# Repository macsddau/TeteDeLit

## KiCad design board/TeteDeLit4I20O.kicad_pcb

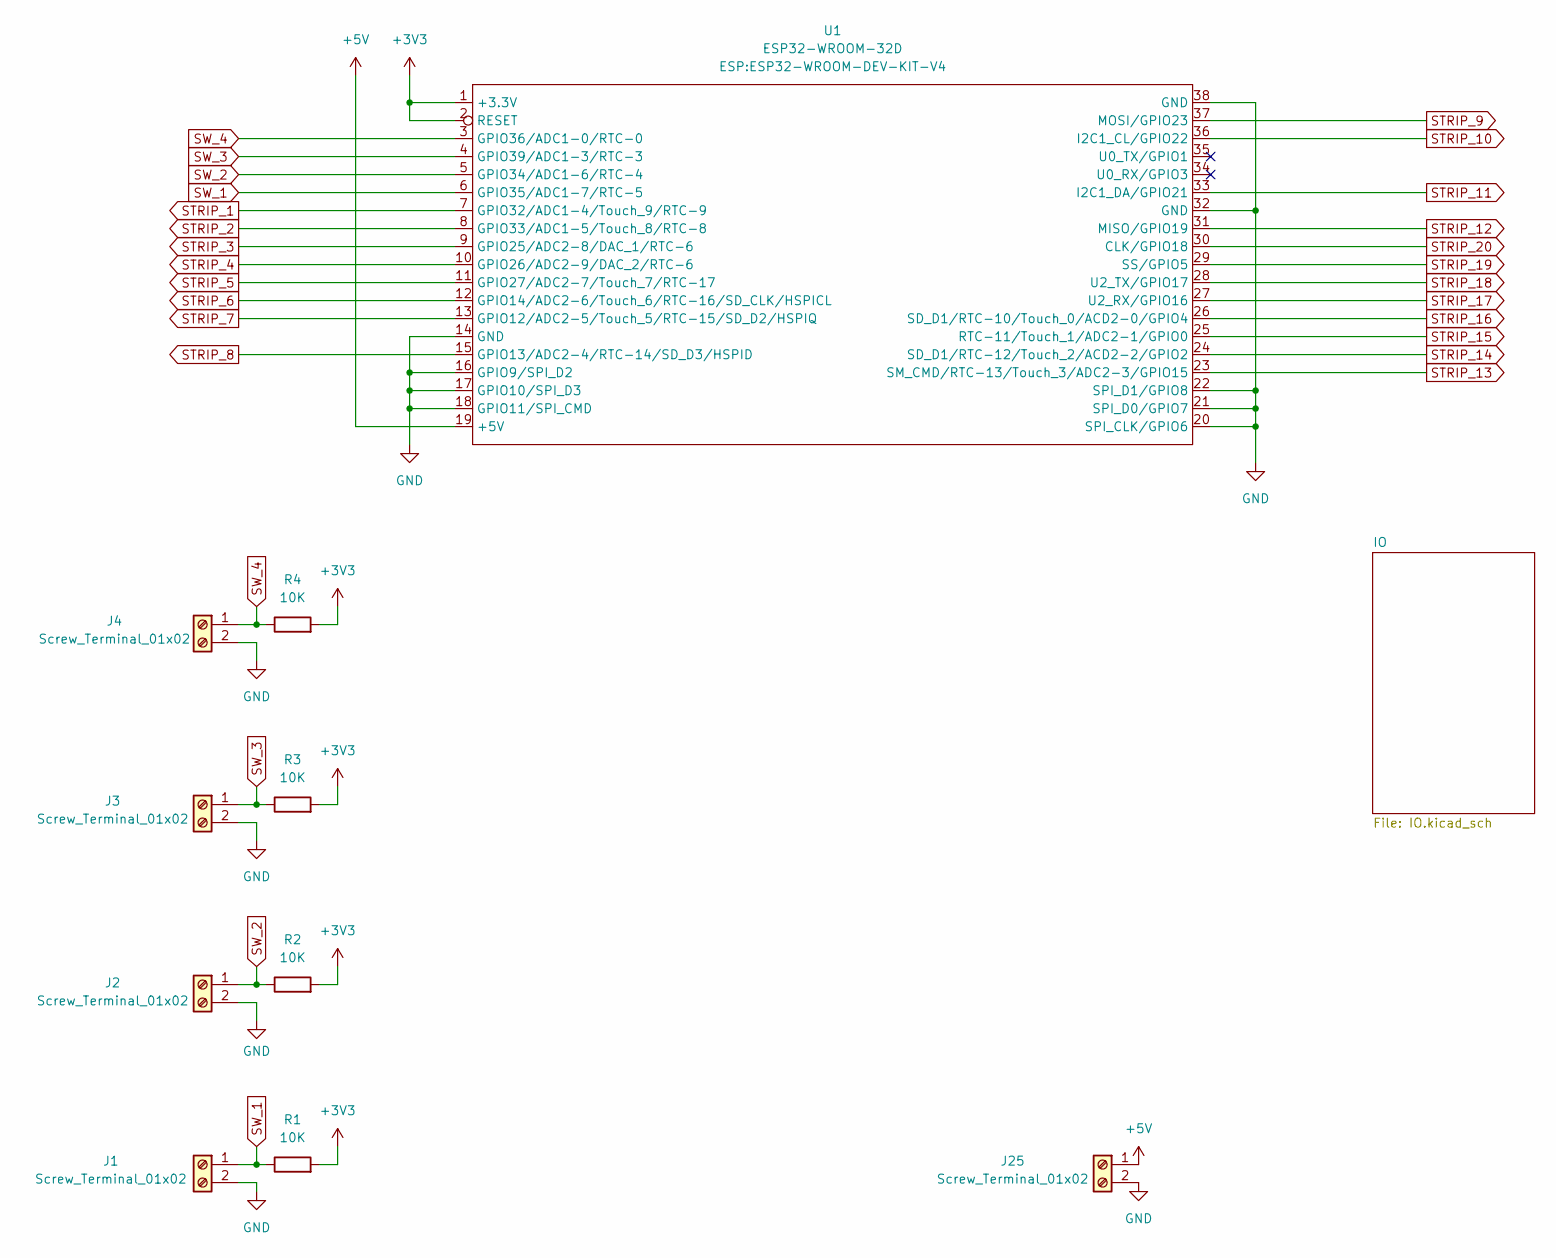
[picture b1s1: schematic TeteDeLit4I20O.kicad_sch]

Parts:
J1, J2, J3, J4, J25: Screw_Terminal_01x02; TerminalBlock_Phoenix_MPT-0,5-2-2.54_1x02_P2.54mm_Horizontal
R1, R2, R3, R4: 10K; R_Axial_DIN0204_L3.6mm_D1.6mm_P5.08mm_Horizontal
U1: ESP32-WROOM-32D; ESP32-WROOM-DEV-KIT-V4

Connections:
+3V3: R1.2, R2.2, R3.2, R4.2, U1.1 (+3.3V), U1.2 (RESET)
+5V: J25.1, U1.19 (+5V); also elsewhere on the board
GND: J1.2, J2.2, J3.2, J4.2, J25.2, U1.14 (GND), U1.16 (GPIO9/SPI_D2), U1.17 (GPIO10/SPI_D3), U1.18 (GPIO11/SPI_CMD), U1.20 (SPI_CLK/GPIO6), U1.21 (SPI_D0/GPIO7), U1.22 (SPI_D1/GPIO8), U1.32 (GND), U1.38 (GND); also elsewhere on the board
STRIP_1: U1.7 (GPIO32/ADC1-4/Touch_9/RTC-9); also elsewhere on the board
STRIP_2: U1.8 (GPIO33/ADC1-5/Touch_8/RTC-8); also elsewhere on the board
STRIP_3: U1.9 (GPIO25/ADC2-8/DAC_1/RTC-6); also elsewhere on the board
STRIP_4: U1.10 (GPIO26/ADC2-9/DAC_2/RTC-6); also elsewhere on the board
STRIP_5: U1.11 (GPIO27/ADC2-7/Touch_7/RTC-17); also elsewhere on the board
STRIP_6: U1.12 (GPIO14/ADC2-6/Touch_6/RTC-16/SD_CLK/HSP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); also elsewhere on the board
STRIP_7: U1.13 (GPIO12/ADC2-5/Touch_5/RTC-15/SD_D2/HSPIQ); also elsewhere on the board
STRIP_8: U1.15 (GPIO13/ADC2-4/RTC-14/SD_D3/HSPID); also elsewhere on the board
STRIP_9: U1.37 (MOSI/GPIO23); also elsewhere on the board
STRIP_10: U1.36 (I2C1_CL/GPIO22); also elsewhere on the board
STRIP_11: U1.33 (I2C1_DA/GPIO21); also elsewhere on the board
STRIP_12: U1.31 (MISO/GPIO19); also elsewhere on the board
STRIP_13: U1.23 (SM_CMD/RTC-13/Touch_3/ADC2-3/GPIO15); also elsewhere on the board
STRIP_14: U1.24 (SD_D1/RTC-12/Touch_2/ACD2-2/GPIO2); also elsewhere on the board
STRIP_15: U1.25 (RTC-11/Touch_1/ADC2-1/GPIO0); also elsewhere on the board
STRIP_16: U1.26 (SD_D1/RTC-10/Touch_0/ACD2-0/GPIO4); also elsewhere on the board
STRIP_17: U1.27 (U2_RX/GPIO16); also elsewhere on the board
STRIP_18: U1.28 (U2_TX/GPIO17); also elsewhere on the board
STRIP_19: U1.29 (SS/GPIO5); also elsewhere on the board
STRIP_20: U1.30 (CLK/GPIO18); also elsewhere on the board
SW_1: J1.1, R1.1, U1.6 (GPIO35/ADC1-7/RTC-5)
SW_2: J2.1, R2.1, U1.5 (GPIO34/ADC1-6/RTC-4)
SW_3: J3.1, R3.1, U1.4 (GPIO39/ADC1-3/RTC-3)
SW_4: J4.1, R4.1, U1.3 (GPIO36/ADC1-0/RTC-0)

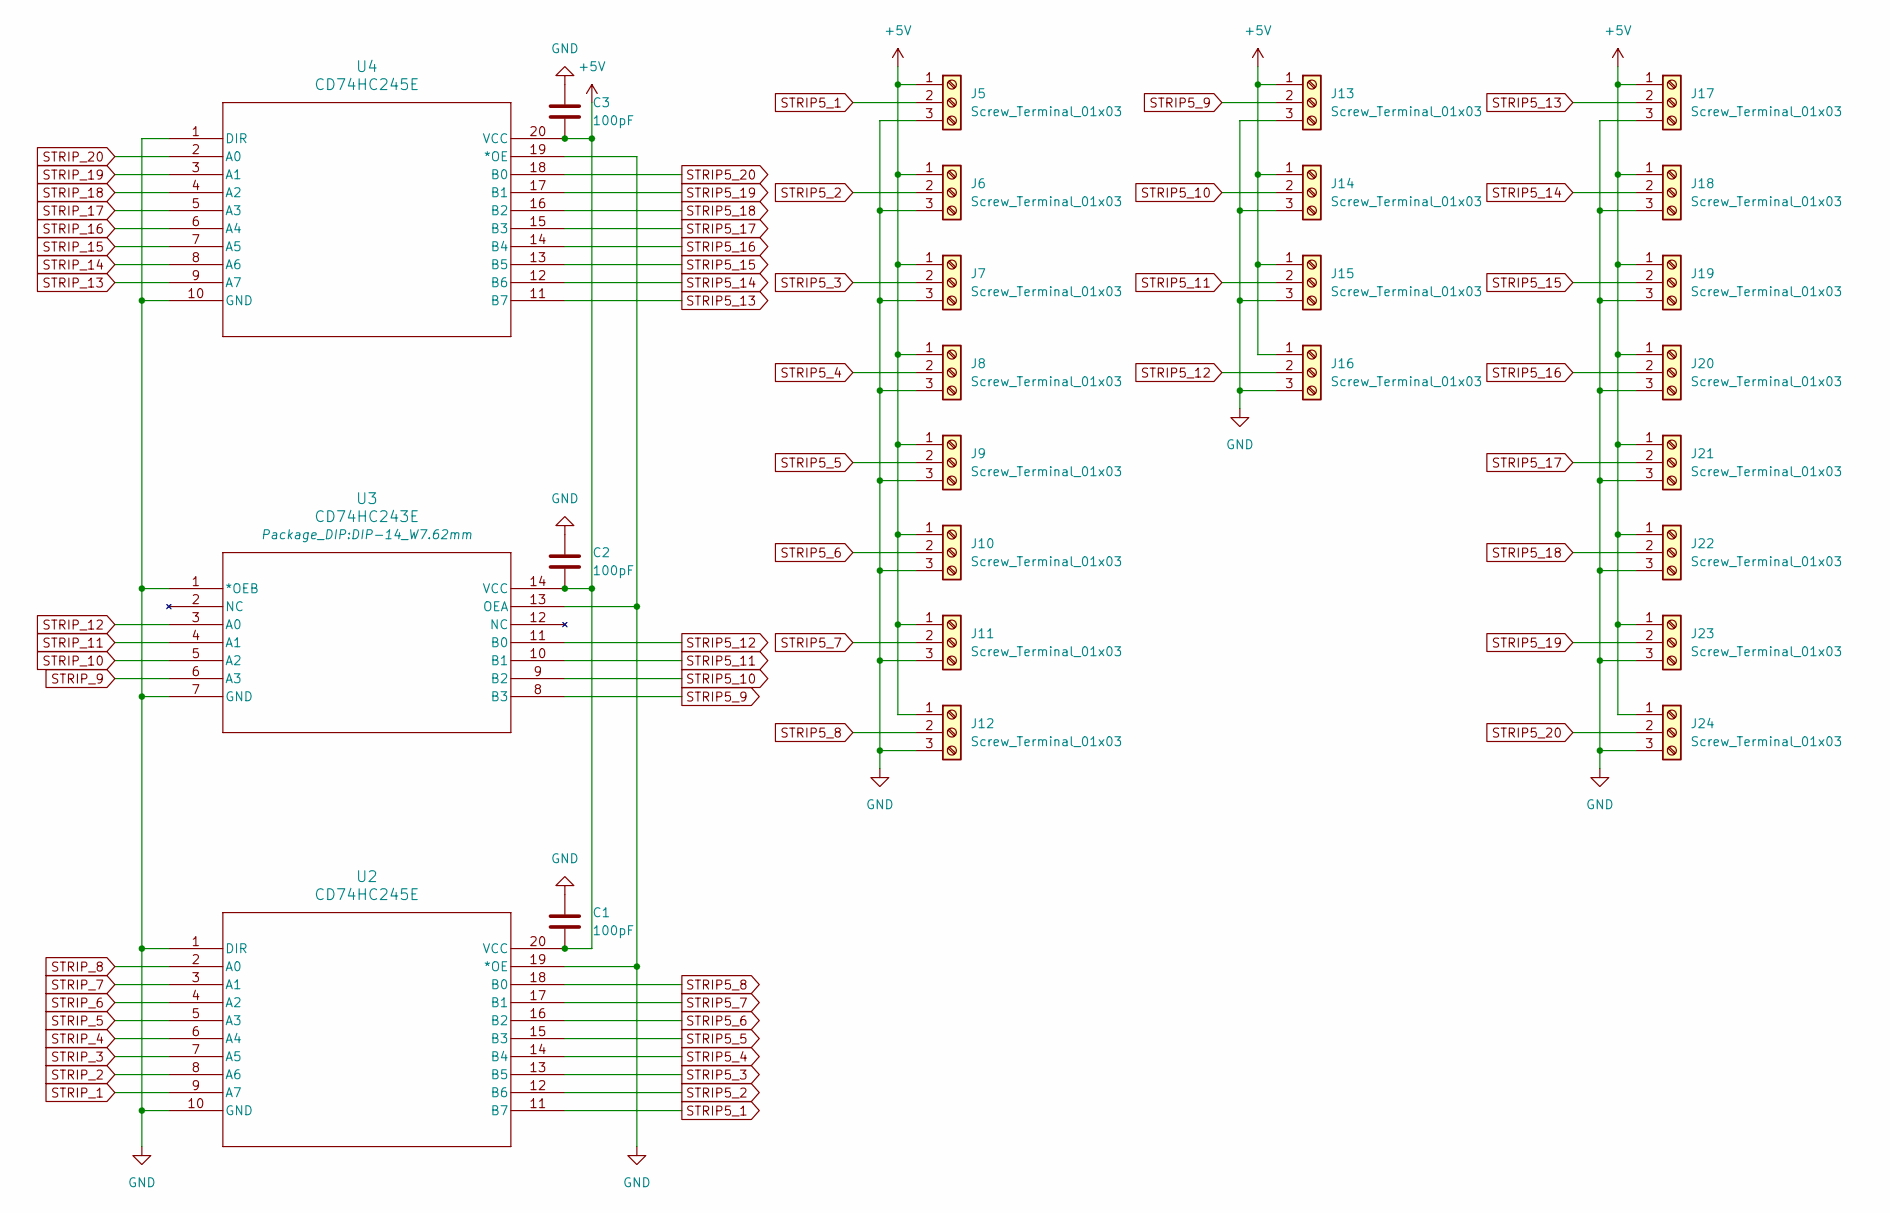
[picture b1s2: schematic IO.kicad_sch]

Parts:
C1, C2, C3: 100pF; C_Disc_D5.0mm_W2.5mm_P2.50mm
J5, J6, J7, J8, J9, J10, J11, J12, J13, J14, J15, J16, J17, J18, J19, J20, J21, J22, J23, J24: Screw_Terminal_01x03; TerminalBlock_Phoenix_MPT-0,5-3-2.54_1x03_P2.54mm_Horizontal
U2, U4: CD74HC245E; DIP-20_W7.62mm
U3: CD74HC243E; DIP-14_W7.62mm

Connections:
+5V: C1.2, C2.2, C3.2, J5.1, J6.1, J7.1, J8.1, J9.1, J10.1, J11.1, J12.1, J13.1, J14.1, J15.1, J16.1, J17.1, J18.1, J19.1, J20.1, J21.1, J22.1, J23.1, J24.1, U2.20 (VCC), U3.14 (VCC), U4.20 (VCC); also elsewhere on the board
GND: C1.1, C2.1, C3.1, J5.3, J6.3, J7.3, J8.3, J9.3, J10.3, J11.3, J12.3, J13.3, J14.3, J15.3, J16.3, J17.3, J18.3, J19.3, J20.3, J21.3, J22.3, J23.3, J24.3, U2.1 (DIR), U2.10 (GND), U2.19 (*OE), U3.1 (*OEB), U3.7 (GND), U3.13 (OEA), U4.1 (DIR), U4.10 (GND), U4.19 (*OE); also elsewhere on the board
STRIP5_1: J5.2, U2.11 (B7)
STRIP5_2: J6.2, U2.12 (B6)
STRIP5_3: J7.2, U2.13 (B5)
STRIP5_4: J8.2, U2.14 (B4)
STRIP5_5: J9.2, U2.15 (B3)
STRIP5_6: J10.2, U2.16 (B2)
STRIP5_7: J11.2, U2.17 (B1)
STRIP5_8: J12.2, U2.18 (B0)
STRIP5_9: J13.2, U3.8 (B3)
STRIP5_10: J14.2, U3.9 (B2)
STRIP5_11: J15.2, U3.10 (B1)
STRIP5_12: J16.2, U3.11 (B0)
STRIP5_13: J17.2, U4.11 (B7)
STRIP5_14: J18.2, U4.12 (B6)
STRIP5_15: J19.2, U4.13 (B5)
STRIP5_16: J20.2, U4.14 (B4)
STRIP5_17: J21.2, U4.15 (B3)
STRIP5_18: J22.2, U4.16 (B2)
STRIP5_19: J23.2, U4.17 (B1)
STRIP5_20: J24.2, U4.18 (B0)
STRIP_1: U2.9 (A7); also elsewhere on the board
STRIP_2: U2.8 (A6); also elsewhere on the board
STRIP_3: U2.7 (A5); also elsewhere on the board
STRIP_4: U2.6 (A4); also elsewhere on the board
STRIP_5: U2.5 (A3); also elsewhere on the board
STRIP_6: U2.4 (A2); also elsewhere on the board
STRIP_7: U2.3 (A1); also elsewhere on the board
STRIP_8: U2.2 (A0); also elsewhere on the board
STRIP_9: U3.6 (A3); also elsewhere on the board
STRIP_10: U3.5 (A2); also elsewhere on the board
STRIP_11: U3.4 (A1); also elsewhere on the board
STRIP_12: U3.3 (A0); also elsewhere on the board
STRIP_13: U4.9 (A7); also elsewhere on the board
STRIP_14: U4.8 (A6); also elsewhere on the board
STRIP_15: U4.7 (A5); also elsewhere on the board
STRIP_16: U4.6 (A4); also elsewhere on the board
STRIP_17: U4.5 (A3); also elsewhere on the board
STRIP_18: U4.4 (A2); also elsewhere on the board
STRIP_19: U4.3 (A1); also elsewhere on the board
STRIP_20: U4.2 (A0); also elsewhere on the board

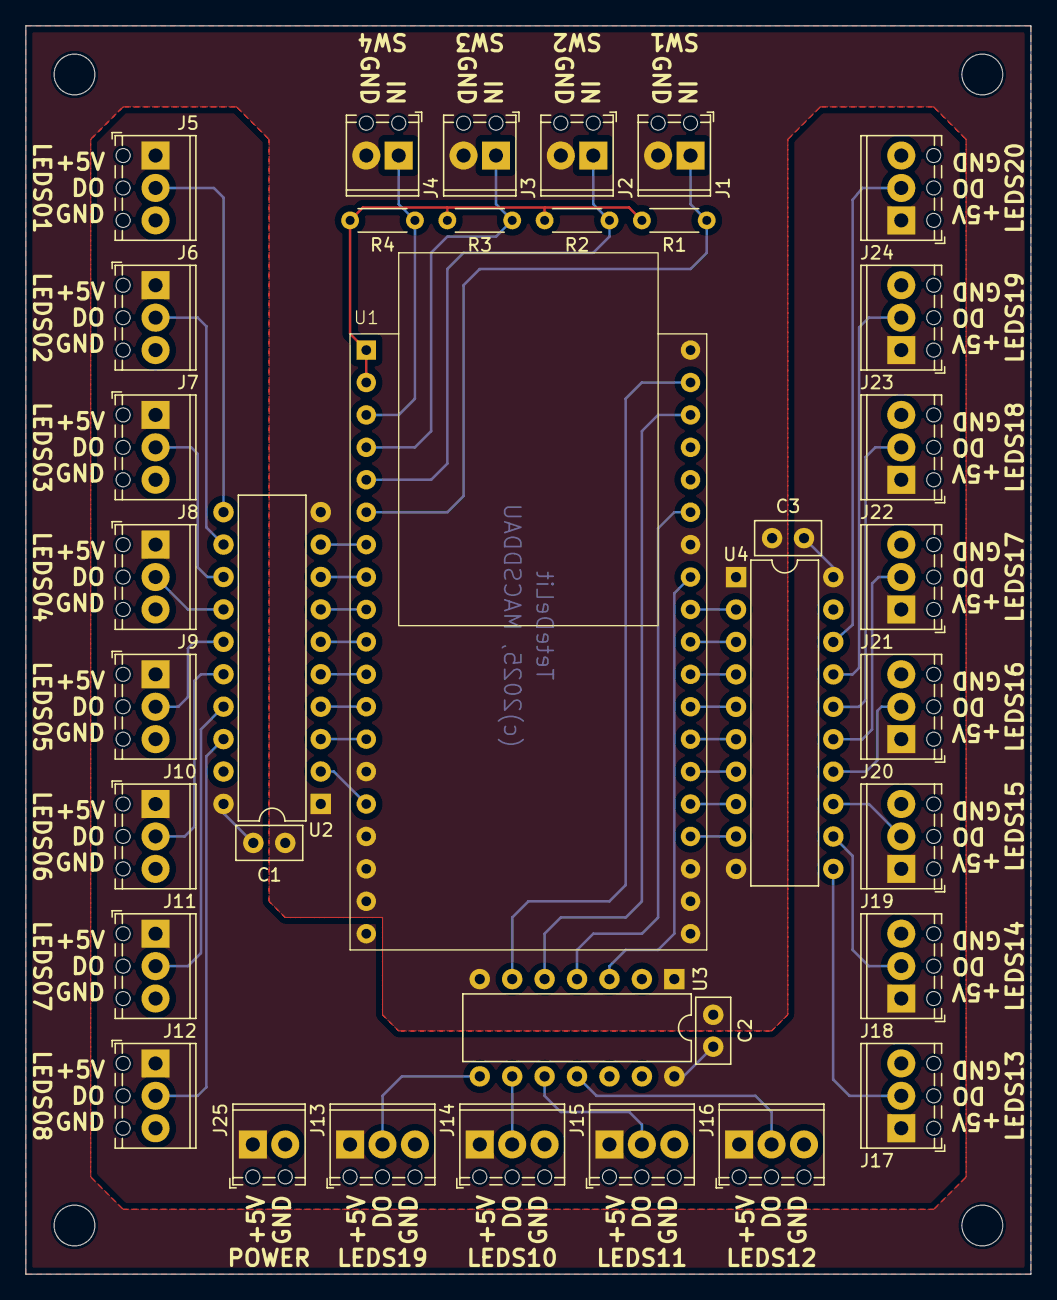
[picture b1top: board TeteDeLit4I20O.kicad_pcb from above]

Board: 2 copper layers, 78.7 x 97.8 mm, 40 parts (0 on the bottom side), 47 nets.

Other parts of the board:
VIS1, VIS2, VIS3, VIS4: MountingHole_3.2mm_M3_DIN965

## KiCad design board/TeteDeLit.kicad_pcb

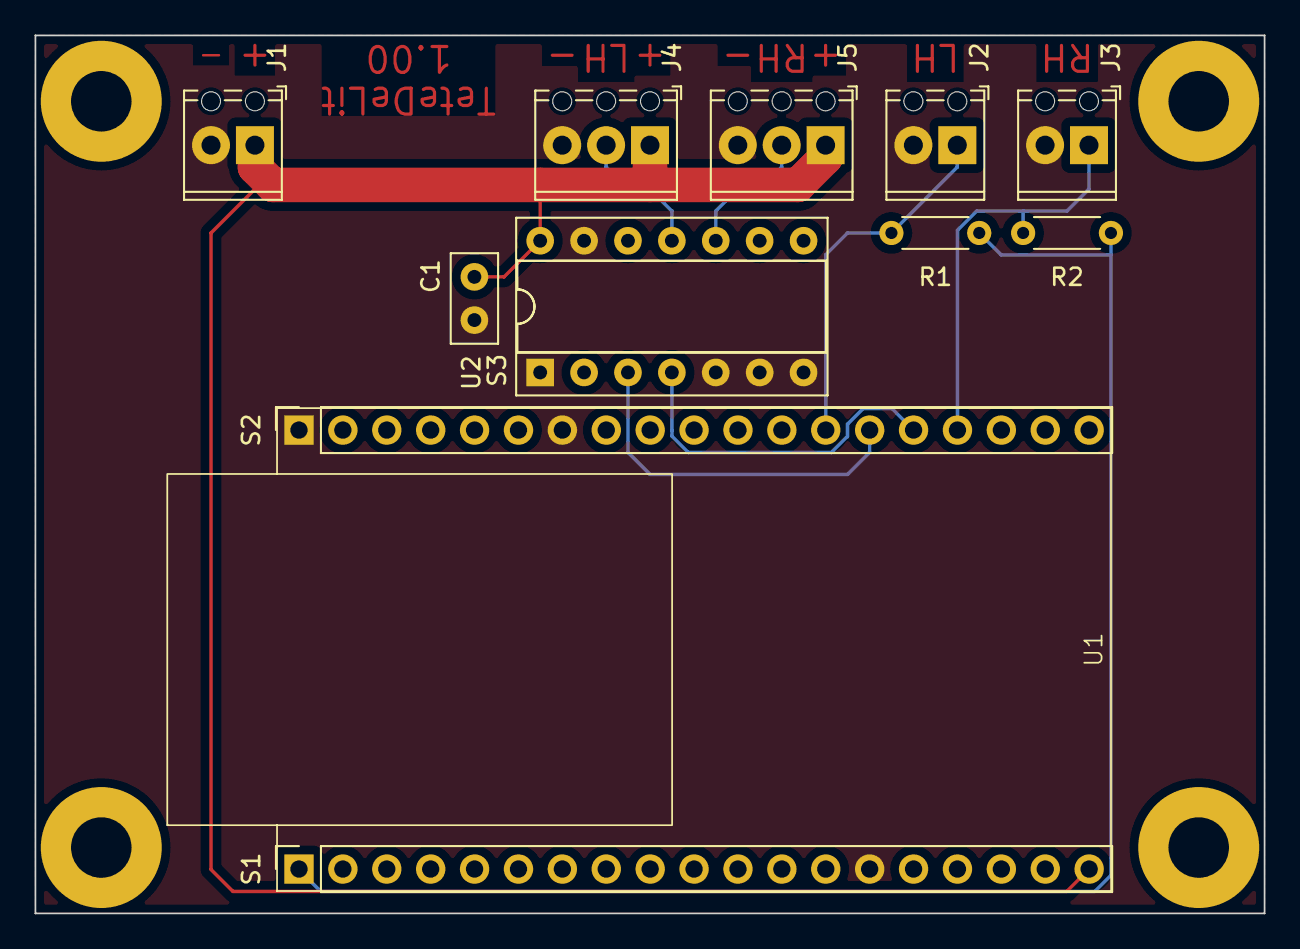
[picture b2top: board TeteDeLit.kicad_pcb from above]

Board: 2 copper layers, 71.1 x 50.8 mm, 17 parts (0 on the bottom side), 9 nets.

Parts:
C1: C; C_Disc_D5.0mm_W2.5mm_P2.50mm
J1, J2, J3: Screw_Terminal_01x02; TerminalBlock_Phoenix_MPT-0,5-2-2.54_1x02_P2.54mm_Horizontal
J4, J5: Screw_Terminal_01x03; TerminalBlock_Phoenix_MPT-0,5-3-2.54_1x03_P2.54mm_Horizontal
R1, R2: R10K; R_Axial_DIN0204_L3.6mm_D1.6mm_P5.08mm_Horizontal
REF01, REF02, REF03, REF04: MountingHole_3.5mm_Pad
S1, S2: Conn_01x19; PinSocket_1x19_P2.54mm_Vertical
S3: DIP-14_W7.62mm_Socket
U1: ESP32-VROOM-32; ESP32-WROOM-DEV-KIT-V4-No_Pin
U2: CD74HC243E; DIP-14_W7.62mm-No_Pin

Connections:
+3V3: R1.1, R2.1, S1.1
+5V: C1.1, J1.1, J4.1, J5.1, S1.19, S3.14
BUTTON_LH: J2.1, R1.2, S2.13
BUTTON_RH: J3.1, R2.2, S2.16
DATA_LH: S2.14, S3.3
DATA_LH_5V: J4.2, S3.11
DATA_RH: S2.15, S3.4
DATA_RH_5V: J5.2, S3.10
GND: C1.2, J1.2, J2.2, J3.2, J4.3, J5.3, S1.14, S2.1, S2.7, S3.1, S3.5, S3.6, S3.7, S3.13

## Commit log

2024-12-28 Works for 2 RGBW 120 leds Strips sides
2024-12-28 Removed unnecessary code. Reoder definitions
2024-12-28 PROGMEM on rgbw variable
2024-12-29 Lock FastLED lib version
2024-12-29 conforms to gnu gcc rules
2024-12-29 Refactor main.h to TeteDeLit.h Move utilities functions to TeteDeLit.cpp
    Add Doxygen support and automation
2024-12-29 Correction in TeteDeLit.cpp documentation
2024-12-31 Adding board
2025-01-01 Light strategy has changed
    It is basicly made for 20 leds srtips with 4 input swiches. But I use only 1 input and 7 strips.
    Board will chnage.
2025-01-01 Bug correction
2025-01-01 Nove lot of def to main prog
2025-01-01 TeteDeLit.h becomes hardware definition
2025-01-01 FastLED include moved
2025-01-02 Piout change according to PCB
2025-01-02 Board update

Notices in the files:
board/TeteDeLit4I20O.kicad_pcb:
(c)2025, MACSDDAU
